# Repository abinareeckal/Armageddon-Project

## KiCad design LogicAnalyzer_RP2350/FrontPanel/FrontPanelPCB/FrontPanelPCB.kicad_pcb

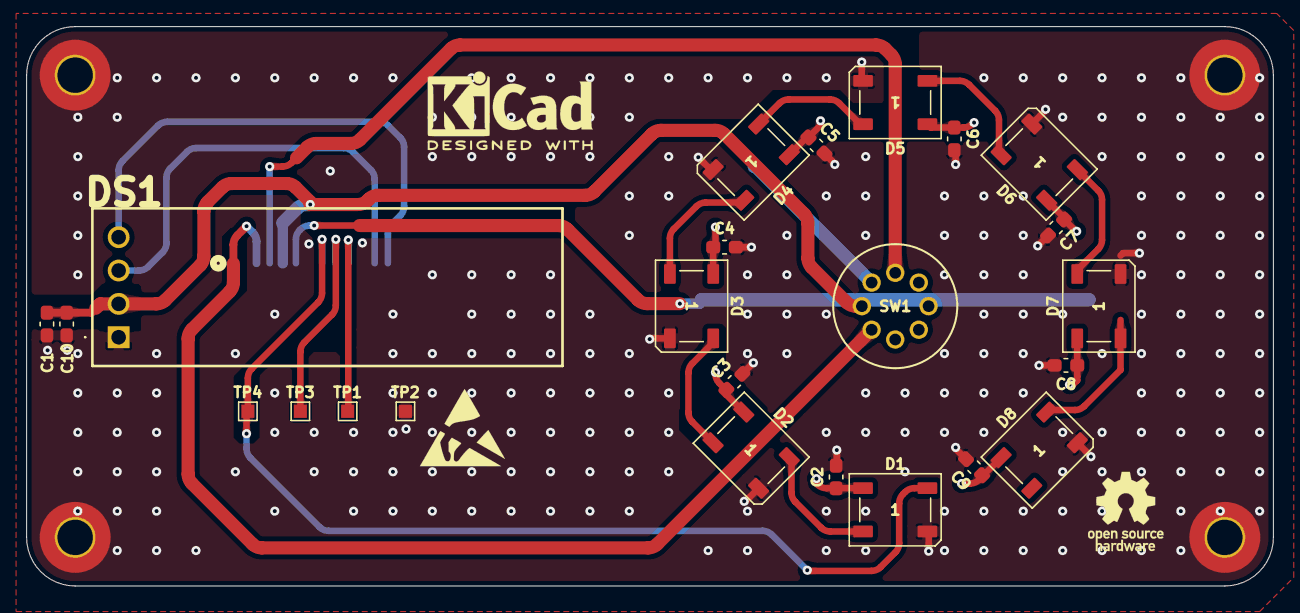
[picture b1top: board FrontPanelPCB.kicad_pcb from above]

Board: 2 copper layers, 95.0 x 42.6 mm, 29 parts (1 on the bottom side), 17 nets.

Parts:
C1, C2, C3, C4, C5, C6, C7, C8, C9: 1uF/50V; C_0603_1608Metric_Pad1.08x0.95mm_HandSolder
C10: 100nF; C_0603_1608Metric_Pad1.08x0.95mm_HandSolder
D1, D2, D3, D4, D5, D6, D7, D8: WS2812B; LED_WS2812B_PLCC4_5.0x5.0mm_P3.2mm
DS1: MDOB128032GV-WI; MDOB128032GVWI
H1, H2, H3, H4: M2.5; MountingHole_2.7mm_M2.5_Pad_TopBottom
J1: 2035571207; CONN_2035570000-SD_12_MOL
SW1: MTL-21-10; MTL-21-10_LRL
TP1, TP2, TP3, TP4: TestPoint_Flag; TestPoint_Pad_1.0x1.0mm

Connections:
+3.3V: C1.1, C10.1, DS1.2 (VIN), J1.3, SW1.3
+5V: C2.1, C3.1, C4.1, C5.1, C6.1, C7.1, C8.1, C9.1, D1.1 (VDD), D2.1 (VDD), D3.1 (VDD), D4.1 (VDD), D5.1 (VDD), D6.1 (VDD), D7.1 (VDD), D8.1 (VDD), J1.4, SW1.2
/EXTVREF: J1.1, SW1.4
/LEDA: D1.4 (DIN), J1.6, TP4.1 (1_1)
/LEDB: J1.7, TP3.1 (1_1)
/LEDC: J1.8, TP1.1 (1_1)
/SCL: DS1.3 (SCL), J1.10
/SDA: DS1.4 (SDA), J1.11
/VREF: J1.2, SW1.1
GND: C1.2, C2.2, C3.2, C4.2, C5.2, C6.2, C7.2, C8.2, C9.2, C10.2, D1.3 (VSS), D2.3 (VSS), D3.3 (VSS), D4.3 (VSS), D5.3 (VSS), D6.3 (VSS), D7.3 (VSS), D8.3 (VSS), DS1.1 (GND), H1.1 (1_1), H2.1 (1_1), H3.1 (1_1), H4.1 (1_1), J1.5, J1.9, J1.12, J1.13 (MP), J1.14 (MP), TP2.1 (1_1)
unnamed: D1.2 (DOUT), D2.4 (DIN)
unnamed: D2.2 (DOUT), D3.4 (DIN)
unnamed: D3.2 (DOUT), D4.4 (DIN)
unnamed: D4.2 (DOUT), D5.4 (DIN)
unnamed: D5.2 (DOUT), D6.4 (DIN)
unnamed: D6.2 (DOUT), D7.4 (DIN)
unnamed: D7.2 (DOUT), D8.4 (DIN)

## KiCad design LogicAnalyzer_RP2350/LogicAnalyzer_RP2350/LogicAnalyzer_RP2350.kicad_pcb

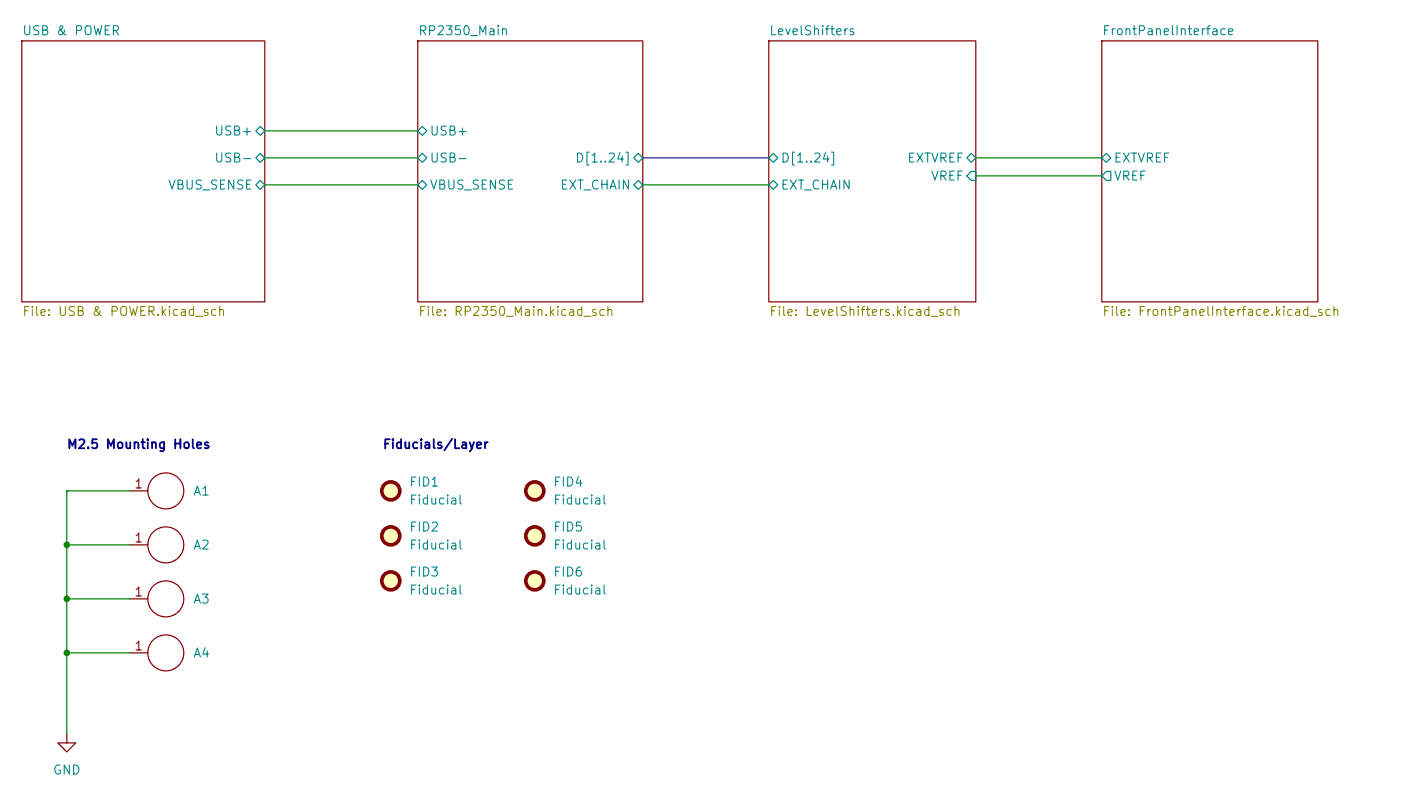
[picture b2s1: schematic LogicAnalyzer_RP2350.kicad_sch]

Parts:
A1, A2, A3, A4: 9774050151R; A_Wurth_WA-SMSI_9774050151R; Part Number 9774050151R
FID1, FID2, FID3, FID4, FID5, FID6: Fiducial; Fiducial_1mm_Mask2mm

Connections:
GND: A1.1 (1_1), A2.1 (1_1), A3.1 (1_1), A4.1 (1_1); also elsewhere on the board

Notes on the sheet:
Fiducials/Layer
M2.5 Mounting Holes

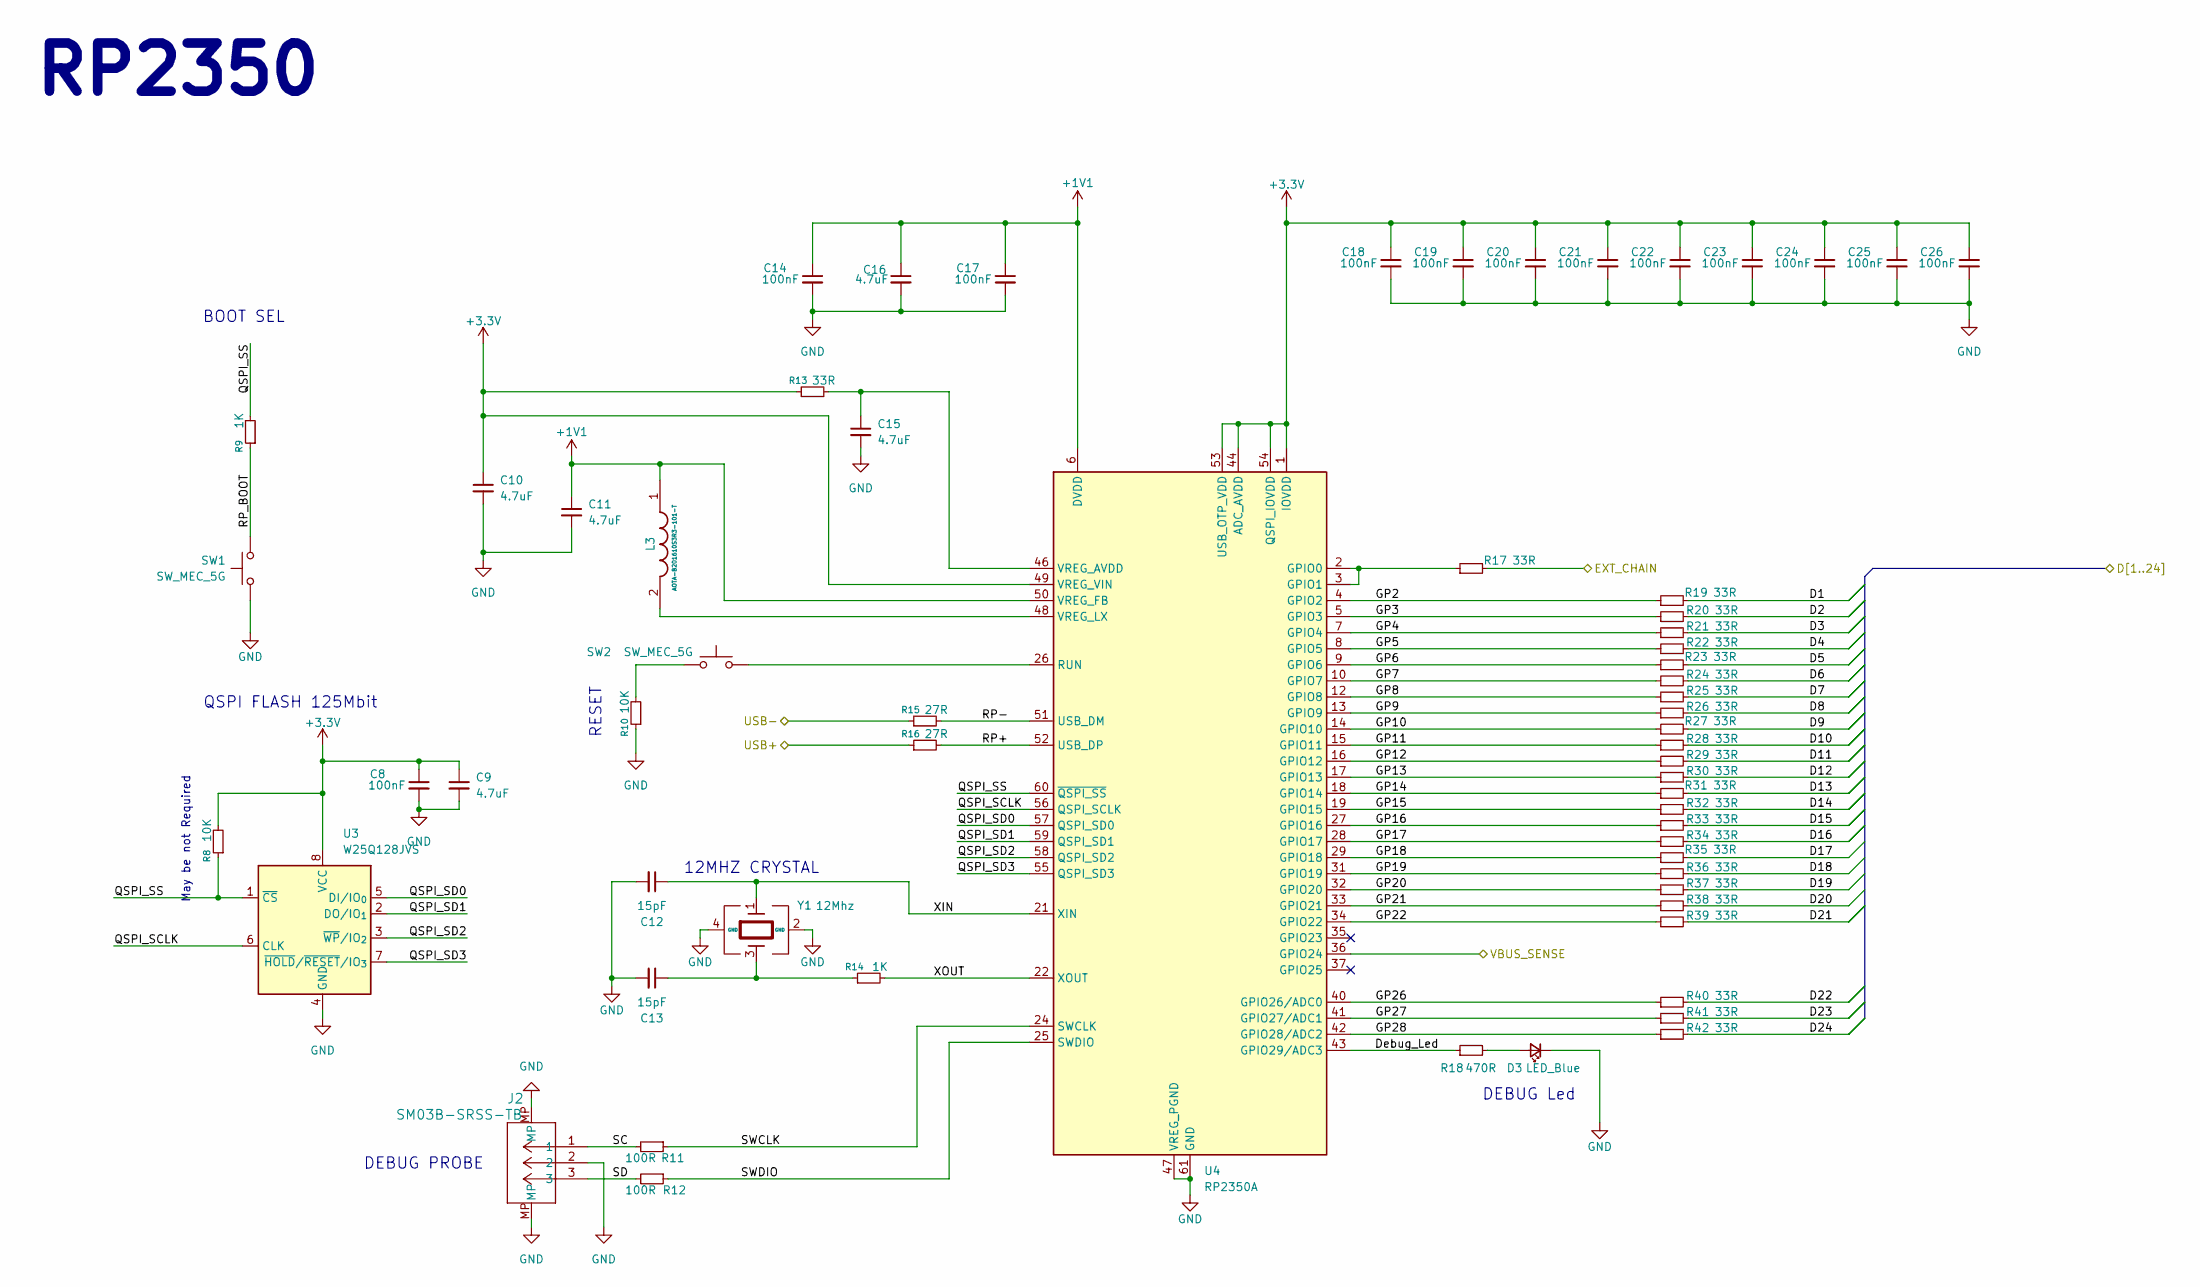
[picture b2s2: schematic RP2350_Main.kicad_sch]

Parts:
C8, C14, C17, C18, C19, C20, C21, C22, C23, C24, C25, C26: 100nF; C_0402_1005Metric_Pad0.74x0.62mm_HandSolder
C9, C15, C16: 4.7uF; C_0402_1005Metric_Pad0.74x0.62mm_HandSolder
C10, C11: 4.7uF; C_0402_1005Metric_small_pads
C12, C13: 15pF; C_0402_1005Metric_Pad0.74x0.62mm_HandSolder
D3: LED_Blue; LED_0603_1608Metric_Pad1.05x0.95mm_HandSolder
J2: SM03B-SRSS-TB; JST_SH_SM03B-SRSS-TB_1x03-1MP_P1.00mm_Horizontal
L3: AOTA-B201610S3R3-101-T; L_pol_2016; Manufacturer_Part_Number AOTA-B201610S3R3-101-T
R8, R10: 10K; R_0603_1608Metric_Pad0.98x0.95mm_HandSolder
R9: 1K; R_0603_1608Metric_Pad0.98x0.95mm_HandSolder
R11, R12: 100R; R_0603_1608Metric_Pad0.98x0.95mm_HandSolder
R13: 33R; R_0603_1608Metric_Pad0.98x0.95mm_HandSolder
R14: 1K; R_0402_1005Metric_Pad0.72x0.64mm_HandSolder
R15, R16: 27R; R_0402_1005Metric_Pad0.72x0.64mm_HandSolder
R17, R19, R20, R21, R22, R23, R24, R25, R26, R27, R28, R29, R30, R31, R32, R33, R34, R35, R36, R37, R38, R39, R40, R41, R42: 33R; R_0402_1005Metric_Pad0.72x0.64mm_HandSolder
R18: 470R; R_0603_1608Metric_Pad0.98x0.95mm_HandSolder
SW1, SW2: SW_MEC_5G; SW4_SKRPABE010_ALPS
U3: W25Q128JVS; SOIC-8_5.3x5.3mm_P1.27mm
U4: RP2350A; QFN-60-1EP_7x7mm_P0.4mm_EP3.4x3.4mm
Y1: 12Mhz; ABM8-272-T3_ABR

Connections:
+1V1: C11.1, C14.1, C16.1, C17.1, L3.1, U4.6 (DVDD), U4.23 (DVDD), U4.39 (DVDD), U4.50 (VREG_FB)
+3.3V: C8.1, C9.1, C10.1, C18.1, C19.1, C20.1, C21.1, C22.1, C23.1, C24.1, C25.1, C26.1, R8.2, R13.1, U3.8 (VCC), U4.1 (IOVDD), U4.11 (IOVDD), U4.20 (IOVDD), U4.30 (IOVDD), U4.38 (IOVDD), U4.44 (ADC_AVDD), U4.45 (IOVDD), U4.49 (VREG_VIN), U4.53 (USB_OTP_VDD), U4.54 (QSPI_IOVDD); also elsewhere on the board
/LevelShifters/D1: R19.2; also elsewhere on the board
/LevelShifters/D2: R20.2; also elsewhere on the board
/LevelShifters/D3: R21.2; also elsewhere on the board
/LevelShifters/D4: R22.2; also elsewhere on the board
/LevelShifters/D5: R23.2; also elsewhere on the board
/LevelShifters/D6: R24.2; also elsewhere on the board
/LevelShifters/D7: R25.2; also elsewhere on the board
/LevelShifters/D8: R26.2; also elsewhere on the board
/LevelShifters/D9: R27.2; also elsewhere on the board
/LevelShifters/D10: R28.2; also elsewhere on the board
/LevelShifters/D11: R29.2; also elsewhere on the board
/LevelShifters/D12: R30.2; also elsewhere on the board
/LevelShifters/D13: R31.2; also elsewhere on the board
/LevelShifters/D14: R32.2; also elsewhere on the board
/LevelShifters/D15: R33.2; also elsewhere on the board
/LevelShifters/D16: R34.2; also elsewhere on the board
/LevelShifters/D17: R35.2; also elsewhere on the board
/LevelShifters/D18: R36.2; also elsewhere on the board
/LevelShifters/D19: R37.2; also elsewhere on the board
/LevelShifters/D20: R38.2; also elsewhere on the board
/LevelShifters/D21: R39.2; also elsewhere on the board
/LevelShifters/D22: R40.2; also elsewhere on the board
/LevelShifters/D23: R41.2; also elsewhere on the board
/LevelShifters/D24: R42.2; also elsewhere on the board
/LevelShifters/EXT_CHAIN: R17.2; also elsewhere on the board
/RP2350_Main/Debug_Led: R18.1, U4.43 (GPIO29/ADC3)
/RP2350_Main/GP2: R19.1, U4.4 (GPIO2)
/RP2350_Main/GP3: R20.1, U4.5 (GPIO3)
/RP2350_Main/GP4: R21.1, U4.7 (GPIO4)
/RP2350_Main/GP5: R22.1, U4.8 (GPIO5)
/RP2350_Main/GP6: R23.1, U4.9 (GPIO6)
/RP2350_Main/GP7: R24.1, U4.10 (GPIO7)
/RP2350_Main/GP8: R25.1, U4.12 (GPIO8)
/RP2350_Main/GP9: R26.1, U4.13 (GPIO9)
/RP2350_Main/GP10: R27.1, U4.14 (GPIO10)
/RP2350_Main/GP11: R28.1, U4.15 (GPIO11)
/RP2350_Main/GP12: R29.1, U4.16 (GPIO12)
/RP2350_Main/GP13: R30.1, U4.17 (GPIO13)
/RP2350_Main/GP14: R31.1, U4.18 (GPIO14)
/RP2350_Main/GP15: R32.1, U4.19 (GPIO15)
/RP2350_Main/GP16: R33.1, U4.27 (GPIO16)
/RP2350_Main/GP17: R34.1, U4.28 (GPIO17)
/RP2350_Main/GP18: R35.1, U4.29 (GPIO18)
/RP2350_Main/GP19: R36.1, U4.31 (GPIO19)
/RP2350_Main/GP20: R37.1, U4.32 (GPIO20)
/RP2350_Main/GP21: R38.1, U4.33 (GPIO21)
/RP2350_Main/GP22: R39.1, U4.34 (GPIO22)
/RP2350_Main/GP26: R40.1, U4.40 (GPIO26/ADC0)
/RP2350_Main/GP27: R41.1, U4.41 (GPIO27/ADC1)
/RP2350_Main/GP28: R42.1, U4.42 (GPIO28/ADC2)
/RP2350_Main/QSPI_SCLK: U3.6 (CLK), U4.56 (QSPI_SCLK)
/RP2350_Main/QSPI_SD0: U3.5 (DI/IO_{0}), U4.57 (QSPI_SD0)
/RP2350_Main/QSPI_SD1: U3.2 (DO/IO_{1}), U4.59 (QSPI_SD1)
/RP2350_Main/QSPI_SD2: U3.3 (~WP/IO_{2}), U4.58 (QSPI_SD2)
/RP2350_Main/QSPI_SD3: U3.7 (~HOLD/~RESET/IO_{3}), U4.55 (QSPI_SD3)
/RP2350_Main/QSPI_SS: R8.1, R9.2, U3.1 (~CS), U4.60 (~QSPI_SS)
/RP2350_Main/RP+: R16.2, U4.52 (USB_DP)
/RP2350_Main/RP-: R15.2, U4.51 (USB_DM)
/RP2350_Main/RP_BOOT: R9.1, SW1.1 (A), SW1.2 (A)
/RP2350_Main/SC: J2.1, R11.2
/RP2350_Main/SD: J2.3, R12.2
/RP2350_Main/SWCLK: R11.1, U4.24 (SWCLK)
/RP2350_Main/SWDIO: R12.1, U4.25 (SWDIO)
/RP2350_Main/USB+: R16.1; also elsewhere on the board
/RP2350_Main/USB-: R15.1; also elsewhere on the board
/RP2350_Main/VBUS_SENSE: U4.36 (GPIO24); also elsewhere on the board
/RP2350_Main/XIN: C12.1, U4.21 (XIN), Y1.1
/RP2350_Main/XOUT: R14.2, U4.22 (XOUT)
GND: C8.2, C9.2, C10.2, C11.2, C12.2, C13.2, C14.2, C15.2, C16.2, C17.2, C18.2, C19.2, C20.2, C21.2, C22.2, C23.2, C24.2, C25.2, C26.2, D3.1 (K), J2.2, J2.MP, R10.1, SW1.3 (B), SW1.4 (B), U3.4 (GND), U4.47 (VREG_PGND), U4.61 (GND), Y1.2 (GND), Y1.4 (GND); also elsewhere on the board
unnamed: C13.1, R14.1, Y1.3
unnamed: D3.2 (A), R18.2
unnamed: R10.2, SW2.3 (B), SW2.4 (B)
unnamed: R17.1, U4.2 (GPIO0), U4.3 (GPIO1)
unnamed: SW2.1 (A), SW2.2 (A), U4.26 (RUN)
unnamed: C15.1, R13.2, U4.46 (VREG_AVDD)
unnamed: L3.2, U4.48 (VREG_LX)

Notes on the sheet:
12MHZ CRYSTAL
BOOT SEL
QSPI FLASH 125Mbit
RP2350
May be not Required
DEBUG Led
RESET
DEBUG PROBE

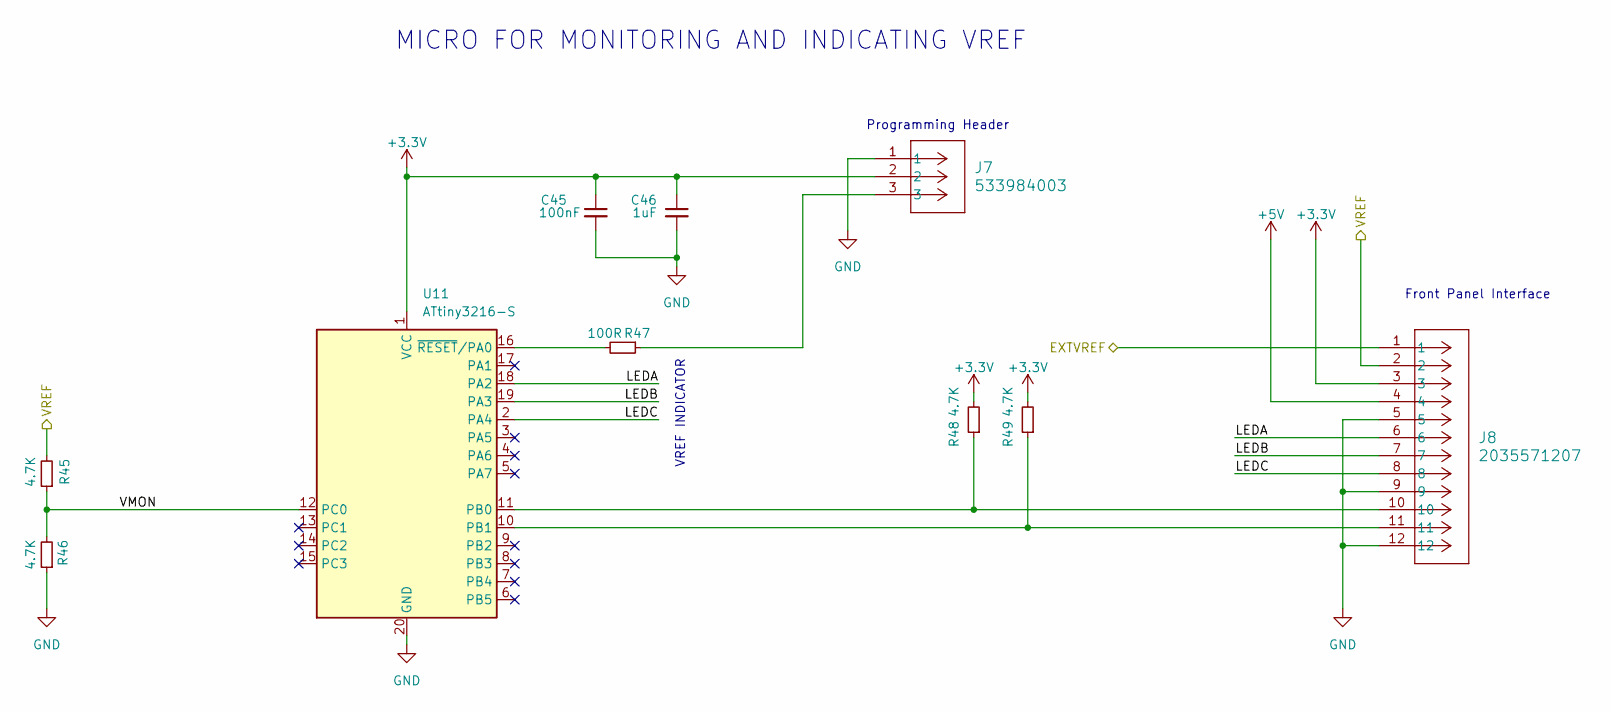
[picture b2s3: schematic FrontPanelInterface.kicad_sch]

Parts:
C45: 100nF; C_0603_1608Metric_Pad1.08x0.95mm_HandSolder
C46: 1uF; C_0603_1608Metric_Pad1.08x0.95mm_HandSolder
J7: 533984003; CONN_533980002-SD_03_MOL
J8: 2035571207; CONN_2035570000-SD_12_MOL
R45, R46, R48, R49: 4.7K; R_0603_1608Metric_Pad0.98x0.95mm_HandSolder
R47: 100R; R_0603_1608Metric_Pad0.98x0.95mm_HandSolder
U11: ATtiny3216-S; SOIC-20W_7.5x12.8mm_P1.27mm

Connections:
+3.3V: C45.1, C46.1, J7.2, J8.3, R48.2, R49.2, U11.1 (VCC); also elsewhere on the board
+5V: J8.4; also elsewhere on the board
/FrontPanelInterface/EXTVREF: J8.1; also elsewhere on the board
/FrontPanelInterface/LEDA: J8.6, U11.18 (PA2)
/FrontPanelInterface/LEDB: J8.7, U11.19 (PA3)
/FrontPanelInterface/LEDC: J8.8, U11.2 (PA4)
/FrontPanelInterface/VMON: R45.1, R46.2, U11.12 (PC0)
/FrontPanelInterface/VREF: J8.2, R45.2; also elsewhere on the board
GND: C45.2, C46.2, J7.1, J7.4 (MP), J7.5 (MP), J8.5, J8.9, J8.12, J8.13 (MP), J8.14 (MP), R46.1, U11.20 (GND); also elsewhere on the board
unnamed: J7.3, R47.1
unnamed: J8.10, R48.1, U11.11 (PB0)
unnamed: J8.11, R49.1, U11.10 (PB1)
unnamed: R47.2, U11.16 (~RESET/PA0)

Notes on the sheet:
VREF INDICATOR
MICRO FOR MONITORING AND INDICATING VREF
Programming Header
Front Panel Interface

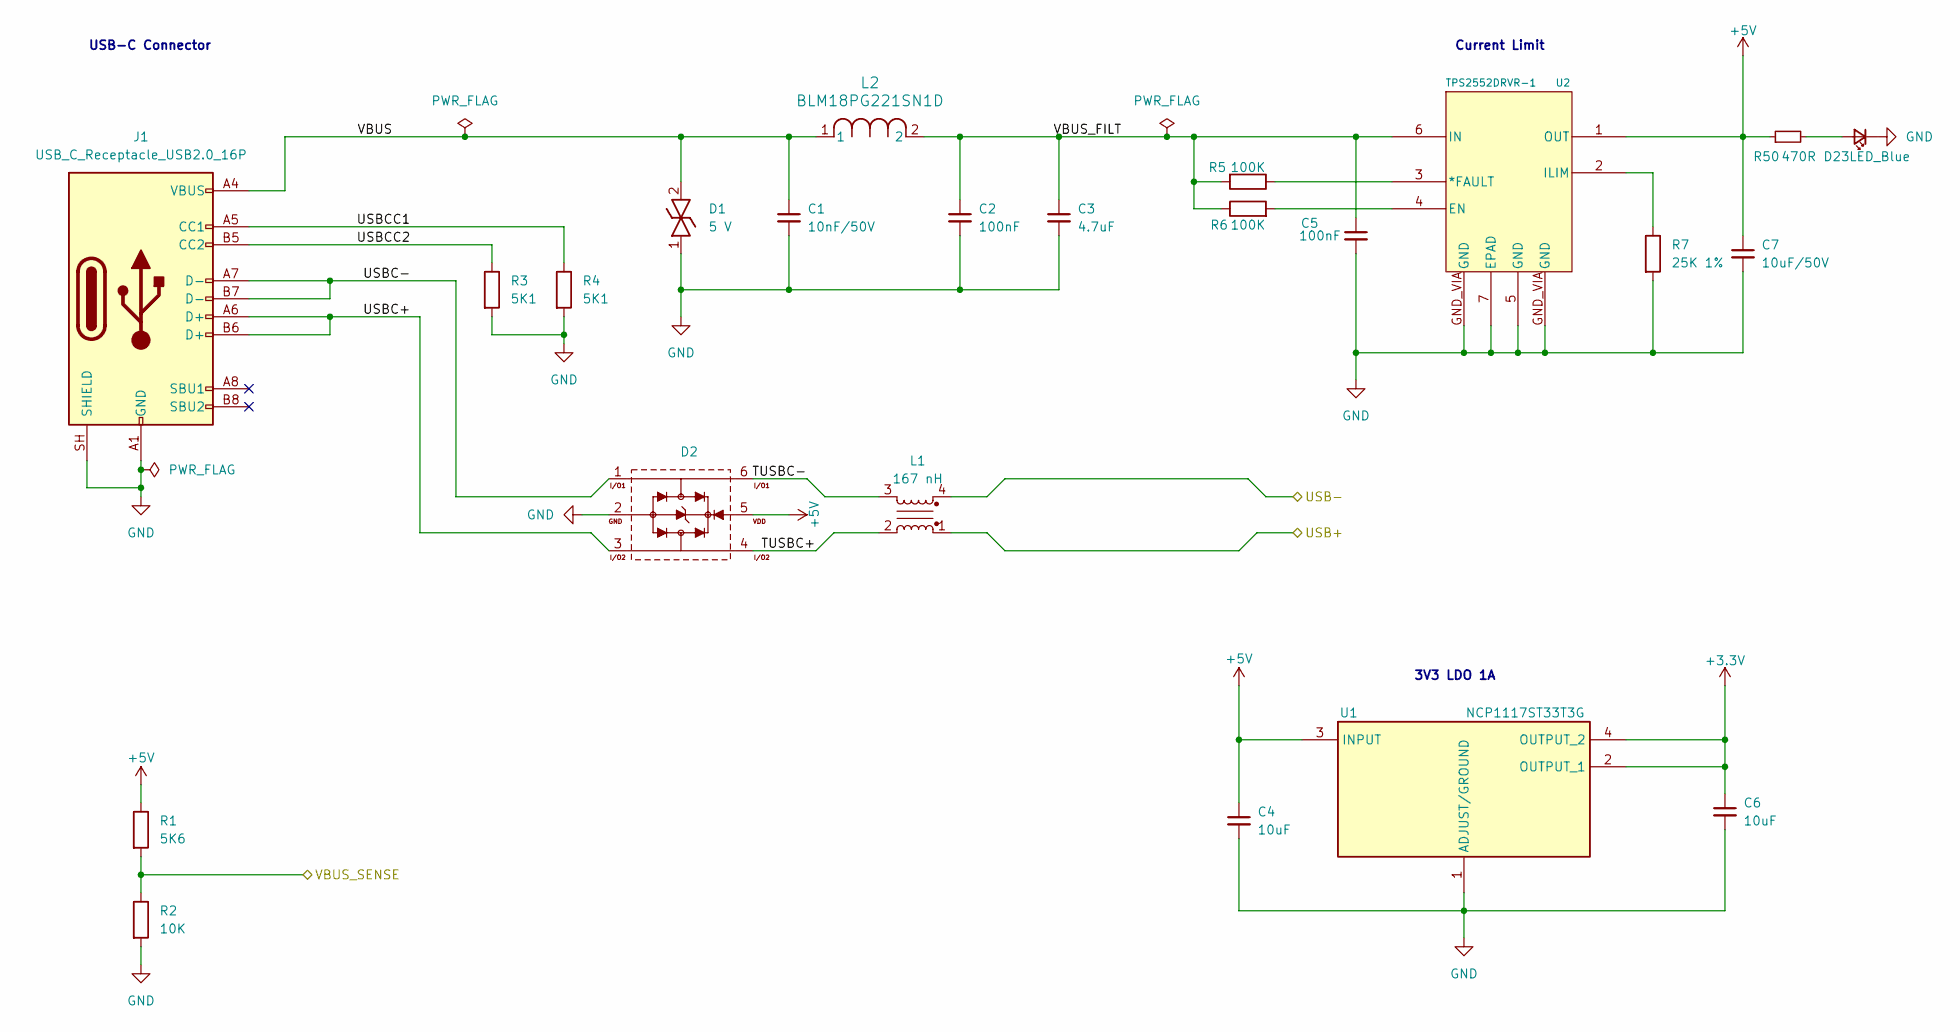
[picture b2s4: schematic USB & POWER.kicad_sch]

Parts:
C1: 10nF/50V; C_0805_2012Metric_Pad1.18x1.45mm_HandSolder
C2: 100nF; C_0805_2012Metric_Pad1.18x1.45mm_HandSolder
C3: 4.7uF; C_0805_2012Metric_Pad1.18x1.45mm_HandSolder
C4, C6: 10uF; C_0805_2012Metric_Pad1.18x1.45mm_HandSolder
C5: 100nF; C_0603_1608Metric_Pad1.08x0.95mm_HandSolder
C7: 10uF/50V; C_0805_2012Metric_Pad1.18x1.45mm_HandSolder
D1: 0402_82307050029; D_Wurth_WE-VE-ULC-0402; Part Number 82307050029
D2: SOT563_82400152; D_Wurth_WE-TVS-SOT563; Part Number 82400152
D23: LED_Blue; LED_0603_1608Metric_Pad1.05x0.95mm_HandSolder
J1: USB_C_Receptacle_USB2.0_16P; USB_C_Receptacle_GCT_USB4105-xx-A_16P_TopMnt_Horizontal
L1: 167 nH; L_Wurth_WE-CNSW-HF-0805; Part Number 744233121
L2: BLM18PG221SN1D; IND_BLM18_0603_MUR
R1: 5K6; R_0603_1608Metric_Pad0.98x0.95mm_HandSolder
R2: 10K; R_0603_1608Metric_Pad0.98x0.95mm_HandSolder
R3, R4: 5K1; R_0603_1608Metric_Pad0.98x0.95mm_HandSolder
R5, R6: 100K; R_0603_1608Metric_Pad0.98x0.95mm_HandSolder
R7: 25K 1%; R_0603_1608Metric_Pad0.98x0.95mm_HandSolder
R50: 470R; R_0603_1608Metric_Pad0.98x0.95mm_HandSolder
U1: NCP1117ST33T3G; SOT230P700X180-4N; Manufacturer_Part_Number NCP1117ST33T3G; Mouser Part Number 863-NCP1117ST33T3G
U2: TPS2552DRVR-1; DRV6_1P6X1

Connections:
+3.3V: C6.1, U1.2 (OUTPUT_1), U1.4 (OUTPUT_2); also elsewhere on the board
+5V: C4.1, C7.1, D2.5 (VDD), R1.1, R50.1, U1.3 (INPUT), U2.1 (OUT); also elsewhere on the board
/RP2350_Main/USB+: L1.1; also elsewhere on the board
/RP2350_Main/USB-: L1.4; also elsewhere on the board
/RP2350_Main/VBUS_SENSE: R1.2, R2.1; also elsewhere on the board
/USB & POWER/TUSBC+: D2.4 (I/O4), L1.2
/USB & POWER/TUSBC-: D2.6 (I/O3), L1.3
/USB & POWER/USBC+: D2.3 (I/O2), J1.A6 (D+), J1.B6 (D+)
/USB & POWER/USBC-: D2.1 (I/O1), J1.A7 (D-), J1.B7 (D-)
/USB & POWER/USBCC1: J1.A5 (CC1), R4.1
/USB & POWER/USBCC2: J1.B5 (CC2), R3.1
/USB & POWER/VBUS: C1.1, D1.2, J1.A4 (VBUS), J1.A9 (VBUS), J1.B4 (VBUS), J1.B9 (VBUS), L2.1
/USB & POWER/VBUS_FILT: C2.1, C3.1, C5.1, L2.2, R5.2, R6.1, U2.6 (IN)
GND: C1.2, C2.2, C3.2, C4.2, C5.2, C6.2, C7.2, D1.1, D2.2 (GND), D23.1 (K), J1.A1 (GND), J1.A12 (GND), J1.B1 (GND), J1.B12 (GND), J1.SH (SHIELD), R2.2, R3.2, R4.2, R7.2, U1.1 (ADJUST/GROUND), U2.5 (GND), U2.7 (EPAD), U2.GND_VIA (GND); also elsewhere on the board
unnamed: D23.2 (A), R50.2
unnamed: R5.1, U2.3 (*FAULT)
unnamed: R6.2, U2.4 (EN)
unnamed: R7.1, U2.2 (ILIM)

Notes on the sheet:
Current Limit
3V3 LDO 1A
USB-C Connector
